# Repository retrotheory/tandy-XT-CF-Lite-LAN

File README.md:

Tandy XT-CF-Lite LAN Rev 0.9a ReadMe
----------------------------
This is a Compact Flash HD and Realtek LAN card for the Tandy 1400. It uses the expansion slot on the rear of the Tandy to add a bootable HD. 
The Realtek 8019AS is an NE2000 compatible. Uses the XT NE2000 packet driver. 

https://www.vcfed.org/forum/forum/genres/pcs-and-clones/41507-ne2000-packet-drivers-for-8-bit-slots

RSET8019.EXE for DOS, can set EEPROM parameters, also includes diagnostic functions

8-bit TANDY (ISA) CompactFlash interface + Boot ROM + LAN

Documentation for the switches can be found on the rear silkscreen. More ROM I/O addresses are possible than the information on the silkscreen. See below.

Credit:
-------
Design uses schematic from Sergey Kiselev, with a few small changes to switches, and PCB from scratch.\
www.malinov.com/Home/sergeys-projects/xt-cf-lite

https://www.lo-tech.co.uk/xt-cf-card-for-tandy-1400-series-laptops/
James Pearce for showing that this was possible a long long time ago.

XT-IDE Universal BIOS\
www.xtideuniversalbios.org  
www.xtideuniversalbios.org/binaries  
Use the latest working binary that includes XTIDECFG.COM (config utility), ide_xt.bin (8086/8088), ide_xtp.bin (80186/V20/V30 and up).

Further documentation:
----------------------

SW1 - ON: ROM Enabled; OFF: ROM Disabled\
SW2 - ON: EEPROM Write Enabled; OFF: EEPROM Write Disabled

---

SW3 - ROM I/O Port:  
123 ROM  
111 C0000  < Tandy Default  
110 C4000  
101 C8000  
101 CA000  
100 CC000  
011 D0000 
010 D4000  
001 D8000  
000 DC000  

Make sure that selected I/O and EEPROM addresses do not conflict with other devices.
Addresses 0xC0000 - 0xC6000 will conflict with EGA/VGA BIOS extension.
Addresses 0xC8000 - 0xCA000 might conflict with XT Hard Disk BIOS extension.
Addresses 0xE0000 and up might conflict with system BIOS on newer motherboards.
It is recommended to disable EEPROM write once XT IDE BIOS extension is programmed and configured.

---

SW4 - IDE I/O Port:  
123 IDE  
111 300 < Default  
011 320  
101 340  
001 360  
110 380  
010 3A0  
100 3C0  
000 3E0  

---

LAN 
Realtek 8019AS 93LC46 EEPROM
Due to height restrictions in the Tandy expansion bay, dont use an IC socket for the U7 93CXX   (93LC46)

---

| References | Value | Footprint | Quantity Per PCB |
|---|---|---|---|
| C1 C2 C3 C4 C5 C6 C15 C16 C17 C18 C19 | 100nF | C_0805_HandSoldering | 11 |
| C20 | 100nF | C_0805_HandSoldering | 1 |
| C7 C8 | 10uF | C_0805_HandSoldering | 2 |
| C21 | 47uF 10V | CP_Tantalum_Case-D_EIA-7343-31_Hand | 1 |
| C9 C10 C11 C12 C13 C14 | C | C_0805_HandSoldering | 6 |
| D1 | IDE LED | LED_D3.0mm | 1 |
| J2 | RJ45_LED_Shielded | 8P8C_yellow_green_Ckmtw_C133529 | 1 |
| J1 | Tandy_PCBEdgeBus_02x30 | Connector_PCBEdge_Tandy1400LT | 1 |
| P1 | CF_CARD | CF_Slot_3M_N7E50-7516TS0884 | 1 |
| P2 | IDE LED | PinHeader_1x02_P2.54mm_Horizontal | 1 |
| R3 | 200R | R_0805_HandSoldering | 1 |
| R5 R6 | 1K | R_0805_HandSoldering | 2 |
| R1 | 5.6k | C_0805_2012Metric_Pad1.15x1.40mm_HandSolder | 1 |
| R2 | 10K | C_0805_2012Metric_Pad1.15x1.40mm_HandSolder | 1 |
| R7 | 10K | R_0805_HandSoldering | 1 |
| R4 | 27k | R_0805_HandSoldering | 1 |
| RN1 RN2 RN3 | 10K | R_Array_Convex_4x1206 | 3 |
| RN4 | 1K | R_Array_Convex_4x1206 | 1 |
| SW4 | IDE Addr | SW_DIP_SPSTx03_Slide_9.78x9.8mm_W7.62mm_P2.54mm | 1 |
| SW3 | ROM Addr | SW_DIP_SPSTx03_Slide_9.78x9.8mm_W7.62mm_P2.54mm | 1 |
| SW1 | ROM Enable | CKCOMP-OS102011MA1QN1 | 1 |
| SW2 | ROM Write Enable | CKCOMP-OS102011MA1QN1 | 1 |
| T1 | 13F-39MNL | SOIC-16W-12_7.5x10.3mm_P1.27mm | 1 |
| U1 | 28C64 | DIP-28_W15.24mm_Socket | 1 |
| U5 | 74LS04 | SOIC-14_3.9x8.7mm_P1.27mm | 1 |
| U4 | 74LS32 | SOIC-14_3.9x8.7mm_P1.27mm | 1 |
| U2 U3 | 74LS688 | SOIC-20W_7.5x12.8mm_P1.27mm | 2 |
| U7 | 93CxxA | IC_DIP8_300 | 1 |
| U6 | RTL8019AS | LQFP-14x20mm_P0.5mmRealtek | 1 |
| Y2 | 20Mhz Crystal | Resonator-2pin_w8.0mm_h3.5mm | 1 |

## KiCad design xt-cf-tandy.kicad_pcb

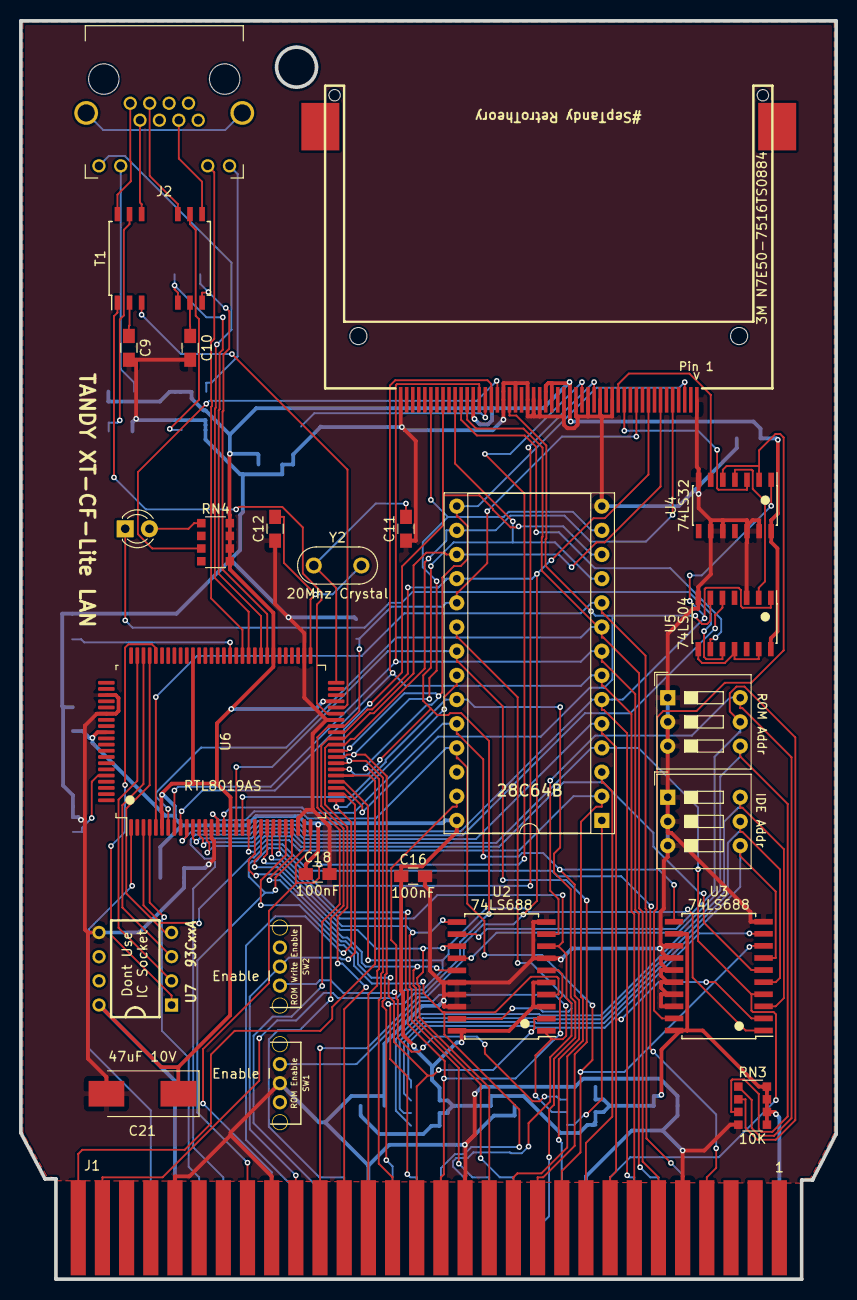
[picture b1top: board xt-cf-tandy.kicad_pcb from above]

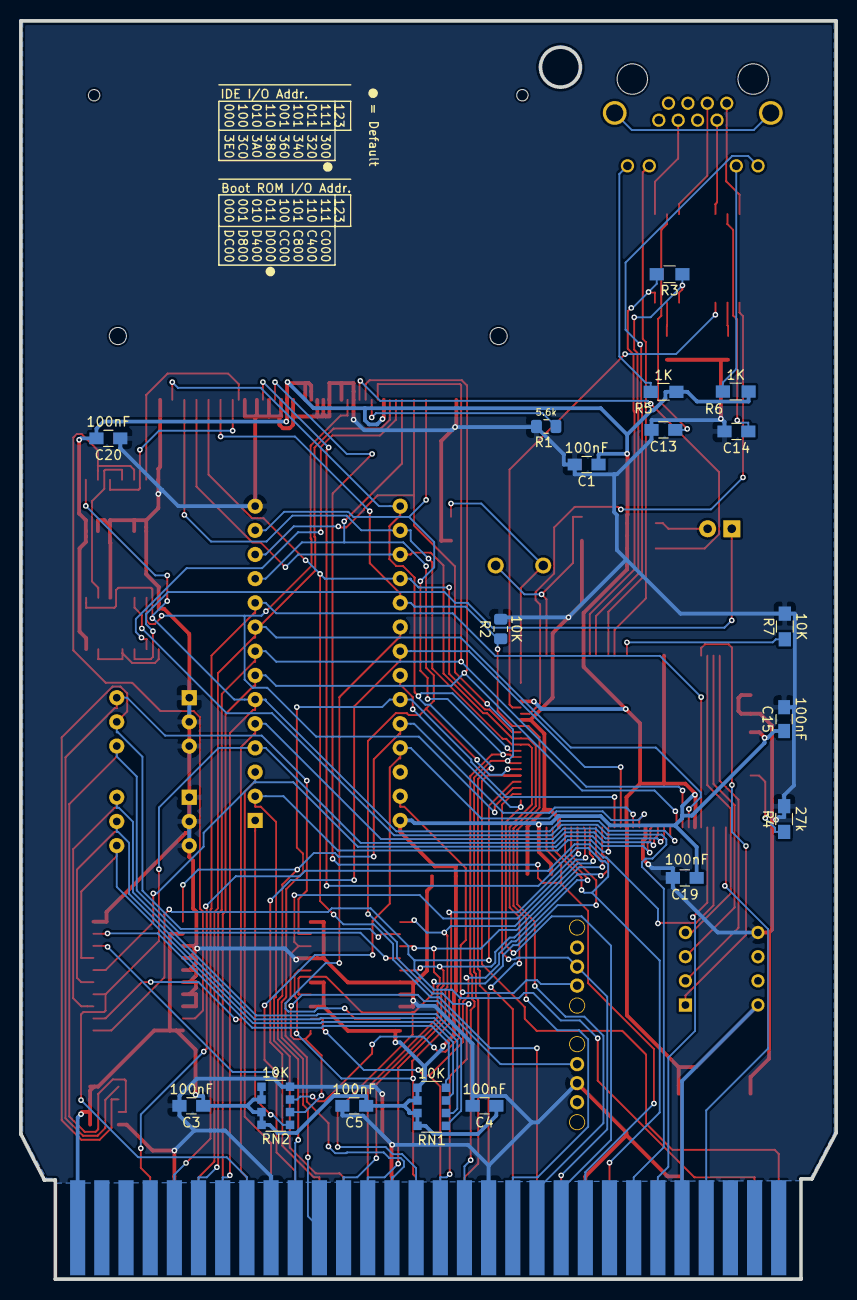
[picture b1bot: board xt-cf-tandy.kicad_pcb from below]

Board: 2 copper layers, 85.7 x 132.2 mm, 44 parts (18 on the bottom side), 86 nets.

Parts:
C1, C3, C4, C5, C15, C16, C18, C19, C20: 100nF; C_0805_HandSoldering
C9, C10, C11, C12, C13, C14: C; C_0805_HandSoldering
C21: 47uF 10V; CP_Tantalum_Case-D_EIA-7343-31_Hand
D1: IDE LED; LED_D3.0mm
J1: Tandy_PCBEdgeBus_02x30; Connector_PCBEdge_Tandy1400LT
J2: RJ45_LED_Shielded; 8P8C_yellow_green_Ckmtw_C133529
P1: CF_CARD; CF_Slot_3M_N7E50-7516TS0884
R1: 5.6k; C_0805_2012Metric_Pad1.15x1.40mm_HandSolder
R2: 10K; C_0805_2012Metric_Pad1.15x1.40mm_HandSolder
R3: 200R; R_0805_HandSoldering
R4: 27k; R_0805_HandSoldering
R5, R6: 1K; R_0805_HandSoldering
R7: 10K; R_0805_HandSoldering
RN1, RN2, RN3: 10K; R_Array_Convex_4x1206
RN4: 1K; R_Array_Convex_4x1206
SW1: ROM Enable; CKCOMP-OS102011MA1QN1
SW2: ROM Write Enable; CKCOMP-OS102011MA1QN1
SW3: ROM Addr; SW_DIP_SPSTx03_Slide_9.78x9.8mm_W7.62mm_P2.54mm
SW4: IDE Addr; SW_DIP_SPSTx03_Slide_9.78x9.8mm_W7.62mm_P2.54mm
T1: 13F-39MNL; SOIC-16W-12_7.5x10.3mm_P1.27mm
U1: 28C64; DIP-28_W15.24mm_Socket
U2, U3: 74LS688; SOIC-20W_7.5x12.8mm_P1.27mm
U4: 74LS32; SOIC-14_3.9x8.7mm_P1.27mm
U5: 74LS04; SOIC-14_3.9x8.7mm_P1.27mm
U6: RTL8019AS; LQFP-14x20mm_P0.5mmRealtek
U7: 93CxxA; IC_DIP8_300
Y2: 20Mhz Crystal; Resonator-2pin_w8.0mm_h3.5mm

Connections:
/A0: J1.10, U1.10, U6.5
/A1: J1.11, P1.20, U1.9, U6.7
/A2: J1.12, P1.19, U1.8, U6.8
/A3: J1.13, P1.18, U1.7, U6.9
/A4: J1.14, U1.6, U4.1, U5.1, U6.10
/A5: J1.15, U1.5, U3.2, U6.11
/A6: J1.16, U1.4, U3.4, U6.12
/A7: J1.17, U1.3, U3.6, U6.13
/A8: J1.19, U1.25, U3.8, U6.15
/A9: J1.20, U1.24, U3.11, U6.16
/A10: J1.21, U1.21, U6.18
/A11: J1.22, U1.23, U6.19
/A12: J1.23, U1.2, U6.20
/A13: J1.24, U2.15, U6.21
/A14: J1.25, U2.13, U6.22
/A15: J1.26, U2.11, U6.23
/A16: J1.28, U2.8, U6.24
/A17: J1.29, U2.6, U6.25
/A18: J1.30, U2.4, U6.26
/A19: J1.31, U2.2, U6.27
/AEN: J1.57, U3.1, U6.34
/CF_DMARQ: P1.43, R1.1
/CF_IORDY: P1.42, RN4.3
/D0: J1.32, P1.21, U1.11, U6.36
/D1: J1.33, P1.22, U1.12, U6.37
/D2: J1.34, P1.23, U1.13, U6.38
/D3: J1.35, P1.2, U1.15, U6.39
/D4: J1.37, P1.3, U1.16, U6.40
/D5: J1.38, P1.4, U1.17, U6.41
/D6: J1.39, P1.5, U1.18, U6.42
/D7: J1.40, P1.6, R2.1, U1.19, U6.43
/IO_READY: J1.59, U6.35
/IRQ2: J1.50, U6.4
/IRQ3: J1.7, U6.3
/IRQ5: J1.54, U6.1
/LED0: J2.9, U6.61
/LED1: J2.11, U6.62
/NX1: C11.2, U6.50, Y2.1
/NX2: C12.2, U6.51, Y2.2
/RDY/~BUSY: RN2.1, U1.1
/RESET: P1.41, U5.6, U6.33
/TPIN+: R3.1, T1.6, U6.59
/TPIN-: R3.2, T1.8, U6.58
/TPOUT+: T1.1, U6.45
/TPOUT-: T1.3, U6.46
/~BRST: J1.48, U5.5
/~CF_CS0: P1.7, U4.3
/~CF_CS1: P1.32, U4.6
/~CF_DASP: P1.45, U5.9
/~IOR: J1.45, P1.34, U6.29
/~IOW: J1.44, P1.35, U6.30
/~MEMR: J1.42, U1.22, U6.31
/~MEMW: J1.41, SW2.2, U6.32
/~ROMW: RN2.3, SW2.3, U1.27
/~ROM_CS: U1.20, U2.19
GND: C1.2, C3.2, C4.2, C5.2, C9.2, C10.2, C11.1, C12.1, C13.2, C14.2, C15.2, C16.2, C18.2, C19.2, C20.1, C21.2, J1.9, J1.18, J1.27, J1.36, J1.43, J1.51, P1.1, P1.8, P1.9, P1.10, P1.11, P1.12, P1.14, P1.15, P1.16, P1.17, P1.39, P1.50, R1.2, R2.2, R4.2, R7.2, RN2.4, RN3.4, SW1.2, SW3.1, SW3.2, SW3.3, SW4.1, SW4.2, SW4.3, U1.14, U2.7, U2.10, U2.16, U2.17, U2.18, U3.10, U3.13, U3.14, U3.15, U3.16, U3.17, U3.18, U4.7, U4.9, U4.10, U4.12, U4.13, U5.3, U5.7, U6.14, U6.28, U6.44, U6.52, U6.83, U6.86, U7.5
unnamed: C9.1, T1.2
unnamed: C10.1, T1.7
unnamed: C13.1, T1.10
unnamed: C14.1, T1.15
unnamed: D1.1, U5.10
unnamed: D1.2, RN4.1
unnamed: J2.1, T1.16
unnamed: J2.2, T1.14
unnamed: J2.3, T1.11
unnamed: J2.6, T1.9
unnamed: J2.10, R6.2
unnamed: J2.12, R5.2
unnamed: R4.1, U6.96
unnamed: R7.1, U6.64
unnamed: RN1.1, SW4.6, U3.3
unnamed: RN1.2, SW4.5, U3.5
unnamed: RN1.3, SW4.4, U3.7
unnamed: RN1.4, U3.9
unnamed: RN2.2, SW1.1, U2.1
unnamed: RN3.1, SW3.6, U2.9
unnamed: RN3.2, SW3.5, U2.12
unnamed: RN3.3, SW3.4, U2.14
unnamed: U3.19, U4.2, U4.5
unnamed: U4.4, U5.2
unnamed: U5.8, U5.11, U5.13
unnamed: U6.76, U7.1
unnamed: U6.77, U7.4
unnamed: U6.78, U7.3
unnamed: U6.79, U7.2
VCC: C1.1, C3.1, C4.1, C5.1, C15.1, C16.1, C18.1, C19.1, C20.2, C21.1, J1.2, J1.52, P1.13, P1.36, P1.38, P1.44, R5.1, R6.1, RN1.5, RN1.6, RN1.7, RN1.8, RN2.5, RN2.6, RN2.7, RN2.8, RN3.5, RN3.6, RN3.7, RN3.8, RN4.5, RN4.6, RN4.7, RN4.8, U1.28, U2.3, U2.5, U2.20, U3.12, U3.20, U4.14, U5.14, U6.6, U6.17, U6.47, U6.57, U6.70, U6.89, U7.8

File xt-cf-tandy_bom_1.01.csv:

Component,Description,Part,References,Value,Footprint,Quantity Per PCB,Datasheet
1,,C-xt-cf-rescue,C1 C2 C3 C4 C5 C6 C15 C16 C17 C18 C19,100nF,C_0805_HandSoldering,11,
2,Unpolarized capacitor,C,C20,100nF,C_0805_HandSoldering,1,~
3,,CP1-xt-cf-rescue,C7 C8,10uF,C_0805_HandSoldering,2,
4,Unpolarized capacitor,C,C21,47uF 10V,CP_Tantalum_Case-D_EIA-7343-31_Hand,1,~
5,Unpolarized capacitor,C,C9 C10 C11 C12 C13 C14,C,C_0805_HandSoldering,6,~
6,Light emitting diode,LED,D1,IDE LED,LED_D3.0mm,1,
7,,RJ45_LED_Shielded,J2,RJ45_LED_Shielded,8P8C_yellow_green_Ckmtw_C133529,1,
8,"Generic connector, single row, 01x30, script generated (kicad-library-utils/schlib/autogen/connector/)",Tandy_PCBEdgeBus_02x30,J1,Tandy_PCBEdgeBus_02x30,Connector_PCBEdge_Tandy1400LT,1,~
9,,CF_CARD-xt-cf-rescue,P1,CF_CARD,CF_Slot_3M_N7E50-7516TS0884,1,
10,,CONN_2-xt-cf-rescue,P2,IDE LED,PinHeader_1x02_P2.54mm_Horizontal,1,
11,Resistor,R,R3,200R,R_0805_HandSoldering,1,~
12,Resistor,R,R5 R6,1K,R_0805_HandSoldering,2,~
13,,R-xt-cf-rescue,R1,5.6k,C_0805_2012Metric_Pad1.15x1.40mm_HandSolder,1,
14,,R-xt-cf-rescue,R2,10K,C_0805_2012Metric_Pad1.15x1.40mm_HandSolder,1,
15,Resistor,R,R7,10K,R_0805_HandSoldering,1,~
16,Resistor,R,R4,27k,R_0805_HandSoldering,1,~
17,"4 resistor network, parallel topology",R_Pack04,RN1 RN2 RN3,10K,R_Array_Convex_4x1206,3,~
18,"4 resistor network, parallel topology",R_Pack04,RN4,1K,R_Array_Convex_4x1206,1,~
19,"3x DIP Switch, Single Pole Single Throw (SPST) switch, small symbol",SW_DIP_x03,SW4,IDE Addr,SW_DIP_SPSTx03_Slide_9.78x9.8mm_W7.62mm_P2.54mm,1,
20,"3x DIP Switch, Single Pole Single Throw (SPST) switch, small symbol",SW_DIP_x03,SW3,ROM Addr,SW_DIP_SPSTx03_Slide_9.78x9.8mm_W7.62mm_P2.54mm,1,
21,"Switch, single pole double throw",SW_SPDT,SW1,ROM Enable,CKCOMP-OS102011MA1QN1,1,
22,"Switch, single pole double throw",SW_SPDT,SW2,ROM Write Enable,CKCOMP-OS102011MA1QN1,1,
23,,13F-39MNL,T1,13F-39MNL,SOIC-16W-12_7.5x10.3mm_P1.27mm,1,
24,,28C64-xt-cf-rescue,U1,28C64,DIP-28_W15.24mm_Socket,1,
25,,74LS04-xt-cf-rescue,U5,74LS04,SOIC-14_3.9x8.7mm_P1.27mm,1,
26,,74LS32-xt-cf-rescue,U4,74LS32,SOIC-14_3.9x8.7mm_P1.27mm,1,
27,,74LS688-xt-cf-rescue,U2 U3,74LS688,SOIC-20W_7.5x12.8mm_P1.27mm,2,
28,"Serial EEPROM, 93 Series, 5.0V, DIP-8/SOIC-8",93CxxA,U7,93CxxA,IC_DIP8_300,1,http://ww1.microchip.com/downloads/en/DeviceDoc/20001749K.pdf
29,,RTL8019AS,U6,RTL8019AS,LQFP-14x20mm_P0.5mmRealtek,1,
30,Two pin crystal,Crystal,Y2,20Mhz Crystal,Resonator-2pin_w8.0mm_h3.5mm,1,~





Component Groups:,30
Component Count:,50
Fitted Components:,50
Number of PCBs:,1
Total components:,50
Schematic Version:,1.01
Schematic Date:,2021-09-29
PCB Variant:,default
BoM Date:,29/09/2021 14:19:13
Schematic Source:,xt-cf-tandy.sch
KiCad Version:,Eeschema (5.1.6)-1
